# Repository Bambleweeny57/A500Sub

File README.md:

# **A500Sub — Amiga A500+ Rev 8A.2 (KiCad Reconstruction)**

A full KiCad reconstruction of the **Commodore Amiga A500+ Rev 8A.2** motherboard, supported with a complete BOM, 3D models, and reference images.  
This project preserves the A500+ Rev 8A.2 board layout in an editable, open format for restoration, repair, and hardware exploration.

---

## 🧭 Project Purpose

The goal of this repository is to provide a clean, accurate, and reproducible version of the **A500+ Rev 8A.2** motherboard for:

- Restoring original A500+ systems  
- Building new boards from scratch  
- Hardware repair and diagnostics  
- Long‑term preservation of Commodore’s design  
- Modding, expansion, and experimentation  

All Gerbers and KiCad sources are included for manufacturing and study.

---

## 📁 Repository Structure

| Folder / File | Description |
|---------------|-------------|
| **`/src`** | Full KiCad project for the A500+ Rev 8A.2 board |
| **`/gerbers`** | Ready‑to‑manufacture Gerber set |
| **`/bom`** | Bill of Materials for component sourcing |
| **`/images`** | Board renders, 3D views, and reference images |
| **`Submeson A500+ gerbers.zip`** | Packaged Gerber archive for PCB fabrication |

---

## 🛠️ Features

### **✔️ Complete KiCad Reconstruction**
- Editable PCB layout  
- Accurate trace routing  
- Includes footprints, netlist, and 3D models  
- Suitable for fabrication without modification  

### **✔️ Manufacturing‑Ready Gerbers**
- Clean, validated Gerber set  
- Provided both in the `/gerbers` folder and as a ZIP archive  

### **✔️ Full BOM Included**
- Component list for building the board  
- Helps with sourcing legacy and modern‑equivalent parts  

### **✔️ 3D Models & Renders**
- Visual reference for assembly  
- Useful for verifying component placement and clearances  

---

## 🧩 About the Amiga A500+ Rev 8A.2

The **A500+** was the final revision of the classic Amiga 500 line, featuring:

- ECS chipset  
- 1 MB Chip RAM  
- Battery‑backed RTC  
- Updated motherboard layout  
- Improved memory and expansion handling  

Rev 8A.2 is one of the later, more stable board revisions, making it ideal for restoration and reproduction.

---

## 🚀 How to Use This Project

### **Open in KiCad**
```bash
git clone https://github.com/Bambleweeny57/A500Sub
```
Open

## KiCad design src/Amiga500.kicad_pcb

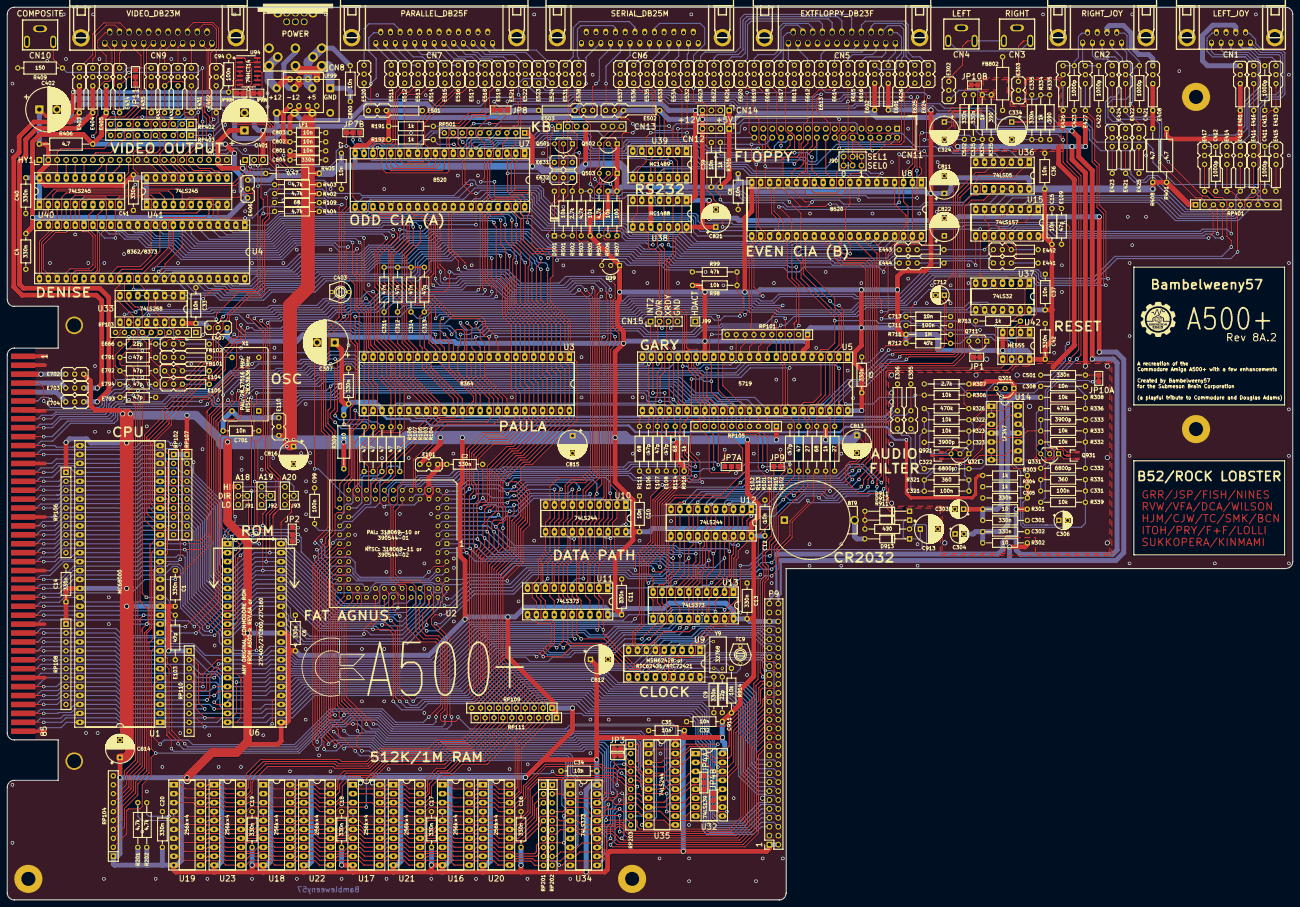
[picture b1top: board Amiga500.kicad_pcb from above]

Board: 2 copper layers, 365.8 x 254.0 mm, 365 parts (0 on the bottom side), 471 nets.

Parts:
BT9: CR2032; Battery_Holder_Coin_2032_BS-7
C1, C2, C3, C4, C5, C6, C9, C11, C13, C14, C16, C17, C18, C19, C20, C40, C41, C42, C804: 330n; C_Axial_L6.3mm_D2.5mm_P10.16mm
C7, C8, C10, C12, C15, C32, C33, C34, C35, C36, C37, C701, C800, C801, C802, C803: 10n; C_Axial_L6.3mm_D2.5mm_P10.16mm
C39, C308, C713: 10n; C_Axial_L9.0mm_D3.2mm_P12.70mm
C94, C99: 100n; C_Axial_L6.3mm_D2.5mm_P10.16mm
C301, C302, C305, C325, C335, C501, C502: 330n; C_Axial_L9.0mm_D3.2mm_P12.70mm
C303, C304: 22u; CP_Radial_D5.0mm_P2.50mm
C306, C712: 10u; CP_Radial_D5.0mm_P2.50mm
C307, C401, C402: 1000u; CP_Radial_D12.5mm_P5.00mm
C311, C312, C313, C314: 47n; C_Axial_L9.0mm_D3.2mm_P12.70mm
C321, C331, C711: 100n; C_Axial_L9.0mm_D3.2mm_P12.70mm
C322, C332: 6800p; C_Axial_L9.0mm_D3.2mm_P12.70mm
C323, C333: 3900p; C_Axial_L9.0mm_D3.2mm_P12.70mm
C324, C334: 22u; CP_Radial_D8.0mm_P5.00mm
C403: 47p; VariCap
C411, C412, C413, C421, C422, C423: 1000p; C_Axial_L9.0mm_D3.2mm_P12.70mm
C811, C812, C813, C814, C815, C816: 100u; CP_Radial_D8.0mm_P5.00mm
C821, C822: 47u; CP_Radial_D8.0mm_P5.00mm
C911: 22p; C_Axial_L6.3mm_D2.5mm_P10.16mm
C913: 4.7u; CP_Radial_D8.0mm_P5.00mm
CN1: LEFT_JOY; DB_9M
CN2: RIGHT_JOY; DB_9M
CN3: RIGHT; SWITCHCRAFT_PJRAN1X1U01X
CN4: LEFT; SWITCHCRAFT_PJRAN1X1U01X
CN5: EXTFLOPPY_DB23F; DB_23F
CN6: SERIAL_DB25M; DB_25M
CN7: PARALLEL_DB25F; DB_25F
CN8: POWER; DS215+DIN8_COMBO
CN9: VIDEO_DB23M; DB_23M
CN10: COMPOSITE; SWITCHCRAFT_PJRAN1X1U01X
CN11: INTERNAL_FLOPPY; IDC-Header_2x17_P2.54mm_Vertical
CN12: FLOPPY_POWER; PinHeader_1x04_P2.54mm_Vertical
CN13: KEYBOARD; Keyboard_Connector
CN14: IDE_POWER; PinHeader_1x04_P2.54mm_Vertical
CN15: IDE_I/F; PinHeader_1x04_P2.54mm_Vertical
D501: 1N4148; D_DO-35_SOD27_P12.70mm_Horizontal
D911, D912, D913: 1n4148; D_DO-35_SOD27_P12.70mm_Horizontal
E101, E110, E406, E407, E702, E703, E704: 10n; EMI_Filter_Short
E102, E103, E106, E107, E108: 47p; C_Axial_L9.0mm_D3.2mm_P12.70mm
E104, E105: 68; EMI_Filter_Long
E109, E791, E792, E793, E794: 47p; C_Axial_L6.3mm_D2.5mm_P10.16mm
E302, E303: 6800p; EMI_Filter_Short
E305, E306: 270p; EMI_Filter_Long
E401, E403, E404, E405, E408, E601, E602: 10n; EMI_Filter_Long
E402, E434: 150p; EMI_Filter_Long
E411, E412, E413, E414, E421, E422, E423, E424: 6800p; EMI_Filter_Long
E415, E416, E417, E425, E426, E427, E441, E442, E443, E444: 470p; EMI_Filter_Long
E431, E432, E433, E435: FERR; EMI_Filter_Long
E501, E502, E503: 47 1/2W; EMI_Filter_Longer
E511, E512, E513, E514, E515, E516, E517, E518, E519, E521, E522, E523, E524, E611, E612, E613, E614, E615, E616, E617, E618, E619, E620, E621, E622, E623, E624, E625, E626, E631, E632: 100p; EMI_Filter_Short
E520, E531, E533, E535, E536, E537, E538: 470p; EMI_Filter_Short
E532, E534: 150p; EMI_Filter_Short
E666: 22p; C_Axial_L6.3mm_D2.5mm_P10.16mm
FB101: 68; EMI_Filter_Long
FB102: 150; EMI_Filter_Long
FB802: Ferrite_Bead_Small; Ferrite_Axial_L9.0mm_D3.2mm_P12.70mm
HY1: VIDIOT; PinHeader_1x22_P2.54mm_Vertical
HY2: COLOR_ANNEX; PinHeader_1x03_P2.54mm_Vertical
J90: DRIVE_SWITCHER; DriveSwitchHeader
J91, J92, J93: Dispatcher_3to1
J99: CONN_HDACT; PinHeader_1x01_P2.54mm_Vertical
JP1, JP3A1, JP3B1, JP10A1, JP10B1, JP99H1, JP99V1: Jumper_2_Bridged; Jumper2-Bridged
JP2, JP7B1, JP8: Jumper_3_Bridged23; Jumper3-Bridged23
JP4A1, JP4B1, JP7A1: Jumper_3_Open; Jumper3-Open
JP9: Jumper_2_Open; Jumper2-Open
JP11: Jumper_3_Bridged12; Jumper3-Bridged12
LF1: L; LineFilter
LF99: CM4545Z131B-10
MT1, MT2, MT4, MT5, MT6, MT7: MountingHole_Pad; MountingHole_4mm_Pad
P1: EXPANSION BUS; A2000_COPRO_SLOT
P9: TRAPDOOR; Trapdoor
Q99, Q301, Q502, Q503: 2N3906; TO-92L_Inline_Wide
Q321, Q331: MPF102; TO-92L_Inline_Wide
Q501, Q711: 2N3904; TO-92L_Inline_Wide
Q921, Q931: MMBFJ113; SOT-23_LongerPads
R98, R306, R308, R322, R323, R332, R333, R339, R501, R505, R506, R914: 10k; R_Axial_DIN0309_L9.0mm_D3.2mm_P12.70mm_Horizontal
R99, R712: 47k; R_Axial_DIN0309_L9.0mm_D3.2mm_P12.70mm_Horizontal
R101, R102: 27; R_Axial_DIN0309_L9.0mm_D3.2mm_P12.70mm_Horizontal
R103, R104, R105, R106, R107, R113: 47; R_Axial_DIN0309_L9.0mm_D3.2mm_P12.70mm_Horizontal
R109, R111, R112, R114: 68; R_Axial_DIN0309_L9.0mm_D3.2mm_P12.70mm_Horizontal
R191, R192, R303, R304, R305, R324, R334, R713, R915, R916: 1k; R_Axial_DIN0309_L9.0mm_D3.2mm_P12.70mm_Horizontal
R201, R202, R402, R403, R404, R503, R504: 4.7k; R_Axial_DIN0309_L9.0mm_D3.2mm_P12.70mm_Horizontal
R301, R302: 10; R_Axial_DIN0309_L9.0mm_D3.2mm_P12.70mm_Horizontal
R307, R502: 2.7k; R_Axial_DIN0309_L9.0mm_D3.2mm_P12.70mm_Horizontal
R309: 10; R_Axial_DIN0309_L9.0mm_D3.2mm_P15.24mm_Horizontal
R321, R331: 360; R_Axial_DIN0309_L9.0mm_D3.2mm_P12.70mm_Horizontal
R325, R335: 390; R_Axial_DIN0309_L9.0mm_D3.2mm_P12.70mm_Horizontal
R326, R336: 470k; R_Axial_DIN0309_L9.0mm_D3.2mm_P12.70mm_Horizontal
R401, R406, R408: 4.7; R_Axial_DIN0309_L9.0mm_D3.2mm_P15.24mm_Horizontal
R405: 0.47; R_Axial_DIN0309_L9.0mm_D3.2mm_P15.24mm_Horizontal
R409: 150; R_Axial_DIN0309_L9.0mm_D3.2mm_P12.70mm_Horizontal
R507: 100; R_Axial_DIN0309_L9.0mm_D3.2mm_P12.70mm_Horizontal
R711: 1M; R_Axial_DIN0309_L9.0mm_D3.2mm_P12.70mm_Horizontal
R911: 470; R_Axial_DIN0309_L9.0mm_D3.2mm_P12.70mm_Horizontal
RP101, RP102, RP105, RP106, RP107, RP108, RP109, RP110, RP111: 4.7k; R_Array_SIP10
RP103: 39; R_Array_SIP10
RP104: 470; R_Array_SIP10
RP201, RP202, RP203: 68; R_Array_SIP10
RP401: 4.7K; R_Array_SIP10
RP402, RP403: 47; R_Array_SIP10
RP501: 10k; R_Array_SIP10
TC9: 6.8-45p; VariCap
U1: 68000D; DIP-64_W22.86mm_Socket_LongPads
U2: FAT_AGNUS_8375; PLCC-84_THT-Socket
U3: PAULA; DIP-48_W15.24mm_Socket_LongPads
U4: DENISE; DIP-48_W15.24mm_Socket_LongPads
U5: GARY_5719; DIP-48_W15.24mm_Socket_LongPads
U6: ROM; DIP-42_W15.24mm_Socket_LongPads
U7, U8: VIA_8520; DIP-40_W15.24mm_Socket_LongPads
U9: MSM6242B; DIP-18_W7.62mm_Socket_LongPads
U10, U12, U35: 74LS244; DIP-20_W7.62mm_Socket_LongPads
U11, U13, U34: 74LS373; DIP-20_W7.62mm_Socket_LongPads
U14: LF347; DIP-14_W7.62mm_Socket_LongPads
U15: 74LS157; DIP-16_W7.62mm_Socket_LongPads
U16, U17, U18, U19, U20, U21, U22, U23: XX4256; DIP-20_W7.62mm_Socket_LongPads
U32: 74LS139; DIP-16_W7.62mm_Socket_LongPads
U33: 74LS258; DIP-16_W7.62mm_Socket_LongPads
U36: 74LS05; DIP-14_W7.62mm_Socket_LongPads
U37: 74LS32; DIP-14_W7.62mm_Socket_LongPads
U38: MC1488; DIP-14_W7.62mm_Socket_LongPads
U39: MC1489; DIP-14_W7.62mm_Socket_LongPads
U40, U41: 74LS245; DIP-20_W7.62mm_Socket_LongPads
U42: NE555; DIP-8_W7.62mm_Socket_LongPads
U94: 74HCT14; SOIC-14_3.9x8.7mm_P1.27mm
X1: XTAL; Oscillator_DIP-14
Y9: 32768; Crystal_RTC

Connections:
7MHZ: E103.1, P1.7, R106.1, U1.15
7MHZ_A: C403.1, E794.1, R107.1, U4.35
+12V: C802.1, C821.1, CN12.4, CN14.4, E404.1, E502.1, E602.1, E704.1, HY2.3, LF1.5, LF99.5, P9.55, R301.1, R911.2, U38.14
+VDC: C301.1, C303.1, Q301.1, R301.2, R307.2, U14.4
-12V: C803.2, C822.2, E403.1, E503.1, E703.1, LF1.6, LF99.6, P9.56, R302.2, U38.1
-VDC: C302.2, C304.2, R302.1, R308.2, U14.11
/Denise & Video Stuff/ab: E433.1, HY1.17
/Denise & Video Stuff/ag: E432.1, HY1.12
/Denise & Video Stuff/ar: E431.1, HY1.7
/Denise & Video Stuff/bb0: HY1.16, RP402.3, U41.15
/Denise & Video Stuff/bb1: HY1.15, U41.16
/Denise & Video Stuff/bb2: HY1.14, U41.17
/Denise & Video Stuff/bb3: HY1.13, RP402.5, U41.18
/Denise & Video Stuff/bcck: HY2.1, RP403.4, U41.14
/Denise & Video Stuff/bcsync_a: RP403.9, U41.12
/Denise & Video Stuff/bcsync_b: HY1.18, U41.11
/Denise & Video Stuff/bg0: HY1.11, U40.11
/Denise & Video Stuff/bg1: HY1.10, U40.12
/Denise & Video Stuff/bg2: HY1.9, U40.13
/Denise & Video Stuff/bg3: HY1.8, RP402.7, U40.14
/Denise & Video Stuff/bpixelsw: RP402.1, U41.13
/Denise & Video Stuff/br0: HY1.6, U40.15
/Denise & Video Stuff/br1: HY1.5, U40.16
/Denise & Video Stuff/br2: HY1.4, U40.17
/Denise & Video Stuff/br3: HY1.3, RP402.9, U40.18
/Denise & Video Stuff/cck_c: E402.1, RP403.3
/Denise & Video Stuff/csync_out: E434.1, JP11.2
/Denise & Video Stuff/hsync_buf: JP99H1.2, RP403.5, U94.6
/Denise & Video Stuff/rbcsync_a: JP11.1, RP403.10
/Denise & Video Stuff/vsync_buf: JP99V1.2, RP403.7, U94.8
/Kickstart ROM/a18_rom: J91.4, U6.2
/Kickstart ROM/a19_rom: J92.4, U6.1
/Kickstart ROM/a20_rom: J93.4, U6.42
/Parallel & Serial/+v: CN6.9, E502.3
/Parallel & Serial/-v: CN6.10, E503.3
/Parallel & Serial/cd: CN6.8, E537.3
/Parallel & Serial/clock: CN13.1, E632.1
/Parallel & Serial/cts: CN6.5, E535.3
/Parallel & Serial/data: CN13.2, E631.1
/Parallel & Serial/dsr: CN6.6, E536.3
/Parallel & Serial/dtr: CN6.20, E531.3
/Parallel & Serial/inuse: CN13.8, Q99.3, Q503.3
/Parallel & Serial/pp0: E512.1, U7.10
/Parallel & Serial/pp1: E513.1, U7.11
/Parallel & Serial/pp2: E514.1, U7.12
/Parallel & Serial/pp3: E515.1, U7.13
/Parallel & Serial/pp4: E516.1, U7.14
/Parallel & Serial/pp5: E517.1, U7.15
/Parallel & Serial/pp6: E518.1, U7.16
/Parallel & Serial/pp7: E519.1, U7.17
/Parallel & Serial/rts: CN6.4, E533.3
/Parallel & Serial/rxd: CN6.3, E534.3
/Parallel & Serial/sel0_out: J90.1, J90.2, U8.13
/Parallel & Serial/sel1_out: J90.5, J90.6, U8.14
/Parallel & Serial/status: CN13.7, Q502.3, R507.1
/Parallel & Serial/txd: CN6.2, E532.3
/Parallel & Serial/~auto: CN7.14, E501.3
/Parallel & Serial/~init: CN7.16, E520.3
/Paula & Audio Stuff/down1: CN1.2, E412.3
/Paula & Audio Stuff/down2: CN2.2, E422.3
/Paula & Audio Stuff/fire1: C411.1, CN1.6, E415.3
/Paula & Audio Stuff/fire2: C421.1, CN2.6, E425.3
/Paula & Audio Stuff/left: E306.1, U3.31
/Paula & Audio Stuff/left1: CN1.3, E413.3
/Paula & Audio Stuff/left2: CN2.3, E423.3
/Paula & Audio Stuff/pot0x: C311.1, E417.1, U3.32
/Paula & Audio Stuff/pot0y: C312.1, E416.1, U3.33
/Paula & Audio Stuff/pot1x: C313.1, E427.1, U3.35
/Paula & Audio Stuff/pot1y: C314.1, E426.1, U3.36
/Paula & Audio Stuff/potx1: C412.1, CN1.5, E417.3
/Paula & Audio Stuff/potx2: C422.1, CN2.5, E427.3
/Paula & Audio Stuff/poty1: C413.1, CN1.9, E416.3
/Paula & Audio Stuff/poty2: C423.1, CN2.9, E426.3
/Paula & Audio Stuff/right: E305.1, U3.30
/Paula & Audio Stuff/right1: CN1.4, E414.3
/Paula & Audio Stuff/right2: CN2.4, E424.3
/Paula & Audio Stuff/up1: CN1.1, E411.3
/Paula & Audio Stuff/up2: CN2.1, E421.3
/Paula & Audio Stuff/vcc1: CN1.7, E401.3
/Paula & Audio Stuff/vcc2: CN2.7, E408.3
/RAM/ma0: RP202.3, U16.6, U17.6, U18.6, U19.6, U20.6, U21.6, U22.6, U23.6
/RAM/ma1: RP202.5, U16.7, U17.7, U18.7, U19.7, U20.7, U21.7, U22.7, U23.7
/RAM/ma2: RP202.7, U16.8, U17.8, U18.8, U19.8, U20.8, U21.8, U22.8, U23.8
/RAM/ma3: RP202.10, U16.9, U17.9, U18.9, U19.9, U20.9, U21.9, U22.9, U23.9
/RAM/ma4: RP201.10, U16.11, U17.11, U18.11, U19.11, U20.11, U21.11, U22.11, U23.11
/RAM/ma5: RP201.8, U16.12, U17.12, U18.12, U19.12, U20.12, U21.12, U22.12, U23.12
/RAM/ma6: RP201.5, U16.13, U17.13, U18.13, U19.13, U20.13, U21.13, U22.13, U23.13
/RAM/ma7: RP201.3, U16.14, U17.14, U18.14, U19.14, U20.14, U21.14, U22.14, U23.14
/RAM/ma8: RP202.1, U16.15, U17.15, U18.15, U19.15, U20.15, U21.15, U22.15, U23.15
/RAM/~bcasl0: JP4A1.1, RP203.7, U32.4
/RAM/~bcasu0: JP4B1.1, RP203.5, U32.12
A1: P1.29, RP107.9, U1.29, U2.60, U6.10
A2: P1.27, P9.45, RP107.8, U1.30, U2.61, U6.9, U9.4
A3: P1.26, P9.46, RP107.7, U1.31, U2.62, U6.8, U9.5
A4: P1.24, P9.47, RP107.6, U1.32, U2.63, U6.7, U9.6
A5: P1.21, P9.48, RP107.5, U1.33, U2.64, U6.6, U9.7
A6: P1.23, RP107.4, U1.34, U2.65, U6.5
A7: P1.28, RP107.2, U1.35, U2.66, U6.4
A8: P1.30, RP107.3, U1.36, U2.67, U6.3, U7.38, U8.38
A9: P1.32, RP106.2, U1.37, U2.68, U6.41, U7.37, U8.37
A10: P1.34, RP106.3, U1.38, U2.69, U6.40, U7.36, U8.36
A11: P1.36, RP106.4, U1.39, U2.70, U6.39, U7.35, U8.35
A12: P1.38, RP106.5, U1.40, U2.71, U6.38, U37.1
A13: P1.39, RP106.6, U1.41, U2.72, U6.37, U37.4
A14: P1.41, RP106.7, U1.42, U2.73, U6.36
A15: P1.43, RP106.8, U1.43, U2.74, U6.35, U36.13
A16: P1.45, RP106.9, U1.44, U2.75, U6.34
A17: P1.47, RP105.8, U1.45, U2.76, U5.33, U6.33
A18: J91.2, P1.52, RP105.7, U1.46, U2.77, U5.34
A19: J92.2, JP2.3, P1.54, RP105.6, U1.47, U5.35
A20: J93.2, P1.56, RP105.5, U1.48, U2.35, U5.36
A21: P1.58, RP105.4, U1.50, U5.37
A22: P1.57, RP105.3, U1.51, U5.38
A23: JP2.1, P1.59, RP105.2, U1.52, U5.39
AUDIN: C501.1, JP10A1.1
AUDOUT: C502.2, JP10B1.2
BDRA0: P9.23, RP202.4, U35.9
BDRA1: P9.24, RP202.6, U35.7
BDRA2: P9.25, RP202.8, U34.9
BDRA3: P9.26, RP202.9, U34.19
BDRA4: P9.27, RP201.9, U34.16
BDRA5: P9.28, RP201.7, U34.6
BDRA6: P9.29, RP201.6, U34.15
BDRA7: P9.30, RP201.4, U34.5
BDRA8: P9.31, RP202.2, U34.12
BDRA9: U32.2, U32.14, U34.2
CCK: E108.1, R103.1, U3.28, U4.36, U5.28, U33.5, U33.6, U35.15, U41.6
CCKQ: E107.1, R104.1, U3.29, U5.27, U33.10, U33.11
CDAC: E793.1, P1.15, RP103.4
D0: P1.75, P9.41, RP110.5, U1.5, U6.14, U7.33, U9.14, U10.2, U11.2
D1: P1.77, P9.42, RP110.6, U1.4, U6.16, U7.32, U9.13, U10.4, U11.5
D2: P1.79, P9.43, RP110.7, U1.3, U6.18, U7.31, U9.12, U10.6, U11.6
D3: P1.81, P9.44, RP110.8, U1.2, U6.20, U7.30, U9.11, U10.8, U11.9
D4: P1.83, RP110.9, U1.1, U6.23, U7.29, U10.11, U11.12
D5: P1.86, RP110.4, U1.64, U6.25, U7.28, U10.13, U11.15
D6: P1.84, RP110.3, U1.63, U6.27, U7.27, U10.15, U11.16
D7: P1.82, RP110.2, U1.62, U6.29, U7.26, U10.17, U11.19
D8: P1.80, RP108.9, U1.61, U6.15, U8.33, U12.2, U13.2
D9: P1.78, RP108.8, U1.60, U6.17, U8.32, U12.4, U13.5
D10: P1.76, RP108.7, U1.59, U6.19, U8.31, U12.6, U13.6
D11: P1.71, RP108.6, U1.58, U6.21, U8.30, U12.8, U13.9
D12: P1.69, RP108.5, U1.57, U6.24, U8.29, U12.11, U13.12
D13: P1.67, RP108.4, U1.56, U6.26, U8.28, U12.13, U13.15
D14: P1.65, RP108.3, U1.55, U6.28, U8.27, U12.15, U13.16
D15: P1.63, RP108.2, U1.54, U6.30, U8.26, U12.17, U13.19
DIR: CN11.18, E623.1, U8.11
DKWE: U3.39, U5.8
DMAL: U2.18, U3.12
DRA0: U2.42, U35.11
DRA1: U2.43, U35.13
DRA2: U2.44, U34.8
DRA3: U2.45, U34.18
DRA4: U2.46, U34.17
DRA5: U2.47, U34.7
DRA6: U2.48, U34.14
DRA7: U2.49, U34.4
DRA8: U2.50, U34.13
DRA9: U2.55, U34.3
DRD0: P9.5, RP111.2, U2.14, U3.10, U4.7, U10.18, U11.3, U16.18, U20.18
DRD1: P9.6, RP109.2, U2.13, U3.9, U4.6, U10.16, U11.4, U16.2, U20.2
DRD2: P9.7, RP111.3, U2.12, U3.7, U4.5, U10.14, U11.7, U16.19, U20.19
DRD3: P9.8, RP109.3, U2.11, U3.6, U4.4, U10.12, U11.8, U16.1, U20.1
DRD4: P9.9, RP111.4, U2.10, U3.5, U4.3, U10.9, U11.13, U17.18, U21.18
DRD5: P9.10, RP109.4, U2.9, U3.4, U4.2, U10.7, U11.14, U17.2, U21.2
DRD6: P9.11, RP111.5, U2.8, U3.3, U4.1, U10.5, U11.17, U17.19, U21.19
DRD7: P9.12, RP109.5, U2.7, U3.2, U4.48, U10.3, U11.18, U17.1, U21.1
DRD8: P9.13, RP111.6, U2.6, U3.1, U4.47, U12.18, U13.3, U18.18, U22.18
DRD9: P9.14, RP109.6, U2.5, U3.48, U4.46, U12.16, U13.4, U18.2, U22.2
DRD10: P9.15, RP111.7, U2.4, U3.47, U4.45, U12.14, U13.7, U18.19, U22.19
DRD11: P9.16, RP109.7, U2.3, U3.46, U4.44, U12.12, U13.8, U18.1, U22.1
DRD12: P9.17, RP111.8, U2.2, U3.45, U4.43, U12.9, U13.13, U19.18, U23.18
DRD13: P9.18, RP109.8, U2.1, U3.44, U4.42, U12.7, U13.14, U19.2, U23.2
DRD14: P9.19, RP111.9, U2.84, U3.43, U4.41, U12.5, U13.17, U19.19, U23.19
DRD15: P9.20, RP109.9, U2.83, U3.42, U4.40, U12.3, U13.18, U19.1, U23.1
E: P1.50, R109.2, U1.20
FC0: P1.31, RP102.4, U1.28
FC1: P1.33, RP102.5, U1.27
FC2: P1.35, RP102.6, U1.26
GND: BT9.2, C1.2, C2.2, C3.2, C4.2, C5.2, C6.2, C7.2, C8.2, C9.2, C10.2, C11.2, C12.2, C13.2, C14.2, C15.2, C16.2, C17.2, C18.2, C19.2, C20.2, C32.2, C33.2, C34.2, C35.2, C36.2, C37.2, C39.2, C40.2, C41.2, C42.2, C94.2, C99.2, C307.2, C401.2, C402.2, C403.2, C411.2, C412.2, C413.2, C421.2, C422.2, C423.2, C701.2, C711.2, C712.2, C713.2, C801.e, C802.2, C803.1, C804.2, C811.2, C812.2, C813.2, C814.2, C815.2, C816.2, C821.2, C822.1, C911.1, C913.2, CN1.0, CN1.8, CN2.0, CN2.8, CN3.1, CN4.1, CN5.0, CN5.3, CN5.4, CN5.5, CN5.6, CN5.7, CN6.0, CN6.7, CN7.0, CN7.17, CN7.18, CN7.19, CN7.20, CN7.21, CN7.22, CN7.23, CN7.24, CN7.25, CN8.2, CN8.6, CN9.0, CN9.13, CN9.16, CN9.17, CN9.18, CN9.19, CN9.20, CN10.1, CN11.1, CN11.5, CN11.7, CN11.9, CN11.11, CN11.13, CN11.15, CN11.17, CN11.19, CN11.21, CN11.23, CN11.25, CN11.27, CN11.29, CN11.31, CN11.33, CN12.2, CN12.3, CN13.6, CN14.2, CN14.3, CN15.4, D501.2, E101.2, E102.2, E103.2, E104.2, E105.2, E106.2, E107.2, E108.2, E109.2, E110.2, E302.2, E303.2, E401.2, E402.2, E403.2, E404.2, E405.2, E406.2, E407.2, E408.2, E411.2, E412.2, E413.2, E414.2, E415.2, E416.2, E417.2, E421.2, E422.2, E423.2, E424.2, E425.2, E426.2, E427.2, E431.2, E432.2, E433.2, E434.2, E435.2, E441.2, E442.2, E443.2, E444.2, E501.2, E502.2, E503.2, E511.2, E512.2, E513.2, E514.2, E515.2, E516.2, E517.2, E518.2, E519.2, E520.2, E521.2, E522.2, E523.2, E524.2, E531.2, E532.2, E533.2, E534.2, E535.2, E536.2, E537.2, E538.2, E601.2, E602.2, E611.2, E612.2, E613.2, E614.2, E615.2, E616.2, E617.2, E618.2, E619.2, E620.2, E621.2, E622.2, E623.2, E624.2, E625.2, E626.2, E631.2, E632.2, E666.2, E702.2, E703.2, E704.2, E791.2, E792.2, E793.2, E794.2, FB101.2, FB102.2, FB802.2, HY1.1, HY1.22, J91.3, J92.3, J93.3, JP7A1.1, JP9.1, LF1.8, LF99.8, MT1.1, MT2.1, MT4.1, MT5.1, MT6.1, MT7.1, P1.1, P1.2, P1.3, P1.4, P1.12, P1.13, P1.25, P1.37, P1.49, P1.61, P1.73, P1.85, P9.3, P9.4, P9.21, P9.22, P9.34, P9.53, P9.54, Q501.1, Q711.1, R409.2, R501.1, RP101.10, RP102.10, RP104.10, RP105.10, RP106.10, RP107.10, RP108.10, RP109.10, RP110.10, RP111.10, RP401.10, TC9.2, U1.16, U1.53, U2.41, U2.58, U2.82, U3.8, U4.37, U5.1, U5.24, U5.40, U6.11, U6.12, U6.31, U7.1, U8.1, U9.9, U10.10, U11.10, U12.10, U13.10, U15.8, U15.15, U16.16, U16.20, U17.16, U17.20, U18.16, U18.20, U19.16, U19.20, U20.16, U20.20, U21.16, U21.20, U22.16, U22.20, U23.16, U23.20, U32.8, U33.8, U33.15, U34.1, U34.10, U35.1, U35.10, U35.19, U36.7, U37.7, U37.10, U37.13, U38.7, U39.7, U40.10, U40.19, U41.10, U41.19, U42.1, U94.7, X1.1, X1.7
GNDA: C301.2, C302.1, C303.2, C304.1, C305.2, C306.2, C308.2, C311.2, C312.2, C313.2, C314.2, C323.2, C333.2, E305.2, E306.2, FB802.1, R304.1, R325.2, R335.2, U3.34
M0H: E443.3, U4.9
M0V: E441.3, U4.38
M1H: E442.3, U4.8
M1V: E444.3, U4.39
unnamed: BT9.1, D913.2
unnamed: C2.1, E101.3, U2.15
unnamed: C3.1, C307.1, R303.2, R309.2, U3.27
unnamed: C9.1, C913.1, D912.1, D913.1, U9.18
unnamed: C33.1, E407.3, U33.16
unnamed: C99.1, U2.40
unnamed: C308.1, Q301.3, R308.1, R326.2, R336.2
unnamed: C321.1, Q321.1, Q921.1, R321.1, R322.2, U14.14
unnamed: C321.2, E306.3, R321.2, U14.13
unnamed: C322.1, C324.1, C325.2, U14.1, U14.2
unnamed: C322.2, R322.1, R323.2
unnamed: C323.1, Q321.2, Q921.2, R323.1, U14.3
unnamed: C324.2, C325.1, JP10B1.1, R324.2
unnamed: C331.1, Q331.1, Q931.1, R331.1, R332.2, U14.8
unnamed: C331.2, E305.3, R331.2, R339.1, U14.9
unnamed: C332.1, C334.1, C335.2, U14.6, U14.7
unnamed: C332.2, R332.1, R333.2
unnamed: C333.1, Q331.2, Q931.2, R333.1, U14.5
unnamed: C334.2, C335.1, R334.2
unnamed: C401.1, HY1.21, R405.2
unnamed: C501.2, CN6.18
unnamed: C502.1, CN6.11
unnamed: C701.1, E110.3, X1.14
unnamed: C711.1, R711.1, U42.2
unnamed: C712.1, R712.1, U42.6, U42.7
unnamed: C713.1, U42.5
unnamed: C800.1, CN8.4, LF1.1, LF99.1
unnamed: C800.2, CN8.1, LF1.2, LF99.2
unnamed: C911.2, U9.17, Y9.3
unnamed: CN3.2, CN4.3, E303.3
unnamed: CN3.3, CN4.2, E302.3
unnamed: CN5.1, E611.3
unnamed: CN5.2, E612.3
unnamed: CN5.8, E613.3
unnamed: CN5.9, E614.3
unnamed: CN5.10, E615.3
unnamed: CN5.11, E616.3
unnamed: CN5.12, E601.3
unnamed: CN5.13, E617.3
unnamed: CN5.14, E618.3
unnamed: CN5.15, E619.3
unnamed: CN5.16, E620.3
unnamed: CN5.17, E621.3
unnamed: CN5.18, E622.3
unnamed: CN5.19, E623.3
unnamed: CN5.20, E624.3
unnamed: CN5.21, E625.3
unnamed: CN5.22, E626.3
unnamed: CN5.23, E602.3
unnamed: CN6.22, E538.3
unnamed: CN7.1, E511.3
unnamed: CN7.2, E512.3
unnamed: CN7.3, E513.3
unnamed: CN7.4, E514.3
unnamed: CN7.5, E515.3
unnamed: CN7.6, E516.3
unnamed: CN7.7, E517.3
unnamed: CN7.8, E518.3
unnamed: CN7.9, E519.3
unnamed: CN7.10, E521.3
unnamed: CN7.11, E522.3
unnamed: CN7.12, E523.3
unnamed: CN7.13, E524.3
unnamed: CN8.3, LF1.4, LF99.4
unnamed: CN8.5, LF1.3, LF99.3
unnamed: CN9.1, RP403.2
unnamed: CN9.3, E431.3
unnamed: CN9.4, E432.3
unnamed: CN9.5, E433.3
unnamed: CN9.6, RP402.4
unnamed: CN9.7, RP402.6
unnamed: CN9.8, RP402.8
unnamed: CN9.9, RP402.10
unnamed: CN9.10, E434.3
unnamed: CN9.11, RP403.6
unnamed: CN9.12, RP403.8
unnamed: CN9.14, RP402.2
unnamed: CN9.15, E402.3
unnamed: CN9.21, E403.3
unnamed: CN9.22, E404.3
unnamed: CN9.23, E405.3
unnamed: CN10.2, E435.3, R409.1
unnamed: D501.1, Q501.2, R501.2, R502.2
unnamed: D911.2, D912.2, R911.1
unnamed: E104.1, RP103.5, U33.7
unnamed: E105.1, RP103.7, U33.9
unnamed: E302.1, R324.1, R325.1
unnamed: E303.1, R334.1, R335.1
unnamed: E401.1, R401.2
unnamed: E408.1, R408.2
unnamed: E411.1, RP401.8, U15.3
unnamed: E412.1, RP401.9, U15.6
unnamed: E413.1, RP401.7, U15.2
unnamed: E414.1, RP401.6, U15.5
unnamed: E421.1, RP401.5, U15.10
unnamed: E422.1, RP401.4, U15.13
unnamed: E423.1, RP401.3, U15.11
unnamed: E424.1, RP401.2, U15.14
unnamed: E435.1, HY1.19
unnamed: E441.1, U15.4
unnamed: E442.1, U15.12
unnamed: E443.1, U15.7
unnamed: E444.1, U15.9
unnamed: E511.1, RP501.10, U7.18
unnamed: E521.1, RP501.6, U7.24
unnamed: E522.1, U8.2, U8.39
unnamed: E523.1, U8.3, U8.40
unnamed: E524.1, Q501.3, RP501.4, U8.4
unnamed: E531.1, U38.11
unnamed: E532.1, U38.8
unnamed: E533.1, U38.6
unnamed: E534.1, U39.1
unnamed: E535.1, U39.4
unnamed: E536.1, U39.10
unnamed: E537.1, U39.13
unnamed: E538.1, R502.1
unnamed: E666.1, FB102.3, U2.34
unnamed: E702.3, P1.5, P1.6
unnamed: E703.3, P1.8
unnamed: E704.3, P1.10
unnamed: FB101.1, X1.8
unnamed: FB101.3, U33.13
unnamed: FB102.1, U33.12
unnamed: HY1.20, JP11.3
unnamed: HY2.2, U4.18
unnamed: J99.1, R98.2, R99.2
unnamed: JP1.1, Q711.3
unnamed: JP2.2, U2.59
unnamed: JP3A1.2, U35.16
unnamed: JP3B1.1, U35.18
unnamed: JP4A1.2, U35.14
unnamed: JP4B1.2, U35.12
unnamed: JP7A1.3, P9.32
unnamed: JP7B1.2, U7.19
unnamed: JP10A1.2, R339.2
unnamed: Q99.2, R99.1
unnamed: Q301.2, R306.1, R307.1
unnamed: Q321.3, Q921.3, R326.1
unnamed: Q331.3, Q931.3, R336.1
unnamed: Q502.2, R503.1
unnamed: Q503.2, R504.1
unnamed: Q711.2, R713.1
unnamed: R101.1, U5.43
unnamed: R102.1, U5.2
unnamed: R103.2, U2.39
unnamed: R104.2, U2.38
unnamed: R105.2, U2.36
unnamed: R106.2, R107.2, U2.37
unnamed: R109.1, U7.25, U8.25
unnamed: R111.1, U5.25
unnamed: R111.2, U11.11, U13.11
unnamed: R112.1, U5.3
unnamed: R112.2, U11.1, U13.1
unnamed: R113.1, U5.4
unnamed: R113.2, U10.1, U10.19, U12.1, U12.19
unnamed: R114.2, U5.21
unnamed: R201.2, RP203.2, U16.4, U16.5, U17.4, U17.5, U18.4, U18.5, U19.4, U19.5, U20.5, U21.5, U22.5, U23.5
unnamed: R202.2, RP203.4, U20.4, U21.4, U22.4, U23.4
unnamed: R306.2, U38.3
unnamed: R713.2, U42.3
unnamed: R914.2, U9.3, U9.15
unnamed: R915.2, U9.2, U36.10
unnamed: RP103.3, U33.4
unnamed: RP203.6, U18.17, U19.17, U22.17, U23.17
unnamed: RP203.8, U16.17, U17.17, U20.17, U21.17
unnamed: RP203.10, U16.3, U17.3, U18.3, U19.3, U20.3, U21.3, U22.3, U23.3
unnamed: TC9.1, U9.16, Y9.1
unnamed: U2.19, U5.19
unnamed: U2.20, U5.15
unnamed: U2.23, U5.18
unnamed: U2.25, U5.20
unnamed: U4.20, U40.5
unnamed: U4.21, U40.4
unnamed: U4.22, U40.3
unnamed: U4.23, U40.2
unnamed: U4.24, U41.5
unnamed: U4.25, U41.4
unnamed: U4.26, U41.3
unnamed: U4.27, U41.2
unnamed: U4.28, U40.9
unnamed: U4.29, U40.8
unnamed: U4.30, U40.7
unnamed: U4.31, U40.6
unnamed: U4.33, U41.7
unnamed: U9.1, Y9.2
unnamed: U32.1, U32.15, U34.11, U35.5
unnamed: U5.47, U36.1
unnamed: U5.46, U36.3
unnamed: U5.45, U36.5
unnamed: U5.44, U36.9
unnamed: U8.8, U38.4
unnamed: U8.9, U38.12
unnamed: U8.6, U39.6
unnamed: U8.5, U39.8
unnamed: U8.7, U39.11
unnamed: U94.4, U94.5
unnamed: U94.9, U94.10
OVL: RP101.9, U5.30, U7.2
RGA1: U2.33, U3.26, U4.17
RGA2: U2.32, U3.25, U4.16
RGA3: U2.31, U3.24, U4.15
RGA4: U2.30, U3.23, U4.14
RGA5: U2.29, U3.22, U4.13
RGA6: U2.28, U3.21, U4.12
RGA7: U2.27, U3.20, U4.11
RGA8: U2.26, U3.19, U4.10
R~W: P1.68, RP101.7, U1.9, U2.22, U5.12, U7.22, U8.22
VAC: C305.1, C306.1, R303.1, R304.2, U14.10, U14.12
VCC: C1.1, C5.1, C6.1, C7.1, C8.1, C10.1, C11.1, C12.1, C13.1, C14.1, C15.1, C16.1, C17.1, C18.1, C19.1, C20.1, C32.1, C34.1, C35.1, C36.1, C37.1, C39.1, C42.1, C801.1, C804.1, C811.1, C812.1, C813.1, C814.1, C815.1, C816.1, CN12.1, CN13.4, CN14.1, D911.1, E101.1, E110.1, E406.1, E407.1, E501.1, E601.1, E702.1, J91.1, J92.1, J93.1, LF1.7, LF99.7, P9.1, P9.2, P9.51, P9.52, Q99.1, Q502.1, Q503.1, R98.1, R191.1, R192.1, R201.1, R202.1, R305.1, R309.1, R401.1, R402.1, R403.1, R404.1, R405.1, R408.1, R505.2, R506.2, R507.2, R711.2, R712.2, R914.1, R915.1, R916.1, RP101.1, RP102.1, RP104.1, RP105.1, RP106.1, RP107.1, RP108.1, RP109.1, RP110.1, RP111.1, RP401.1, RP501.1, U1.14, U1.49, U5.6, U5.17, U5.48, U6.22, U6.32, U7.20, U8.20, U10.20, U11.20, U12.20, U13.20, U15.16, U16.10, U17.10, U18.10, U19.10, U20.10, U21.10, U22.10, U23.10, U32.16, U34.20, U35.20, U36.14, U37.14, U38.5, U38.10, U38.13, U39.14, U42.4, U42.8
VD: C40.1, C41.1, C94.1, C402.1, HY1.2, R406.1, U40.1, U40.20, U41.1, U41.20, U94.1, U94.13, U94.14
VDDA: C4.1, E405.1, E406.3, R406.2, U4.19
XCLK: R404.2, RP403.1, U33.14
XRDY: CN15.3, P1.18, RP104.8, U5.31
~AS: P1.74, RP101.8, U1.6, U2.24, U5.13
~BCASL1: JP4A1.3, P9.35, U32.5
~BCASU1: JP4B1.3, P9.36, U32.11
~BEER: P1.46, RP104.5, U1.22
~BGACK: P1.62, RP104.6, U1.12, U5.14
~BG: P1.64, U1.11
~BRAS0: JP3B1.2, P9.38, RP203.1
~BRAS1: JP3A1.1, P9.37, RP203.3
~BR: P1.60, RP104.7, U1.13
~BWE: P9.39, RP203.9, U35.3
~CASL: U2.53, U32.3, U35.6
~CASU: U2.54, U32.13, U35.8
~CCKQ_A: E105.3, E109.1, U15.1
~CCKQ: E791.1, P1.14, RP103.8
~CCK_A: E102.1, E104.3, P9.40
~CCK: E792.1, P1.16, RP103.6
~CDAC: E106.1, R105.1, U4.34, U5.26, U33.2, U33.3
~CHNG: CN11.2, E616.1, U7.4
~CLKCS: JP9.2, P9.33, R916.2, U36.11, U36.12
~CLKRD: P9.49, U5.22, U9.8
~CLKWR: P9.50, U5.23, U9.10
~CSYNC: U2.80, U4.32, U41.8, U41.9
~DKRD: CN11.30, E612.1, R305.2, U3.37
~DKWDB: CN11.22, E621.1, U36.6
~DKWD: U3.38, U5.9
~DKWEB: CN11.24, E620.1, U36.8
~DTACK: P1.66, R101.2, RP104.2, U1.10
~EVEN_CIA: U8.23, U37.6
~EXTICK: JP7A1.2, JP7B1.1, RP501.9, U5.32
~FIRE0: E415.1, JP8.1, U7.8
~FIRE1: E425.1, JP8.3, U7.9
~HLT: P1.55, RP101.3, U1.17, U5.42
~HSYNC: JP99H1.1, R402.2, U2.81, U8.19, U94.3
~INDEX: CN11.8, E626.1, RP501.7, U8.24
~INT2: CN15.1, P1.19, R191.2, U3.16, U7.21
~INT3: U2.17, U3.17
~INT6: P1.22, R192.2, U3.18, U8.21
~IORESET: E520.1, E615.1, U37.8
~IPL0: P1.40, RP102.7, U1.25, U3.13
~IPL1: P1.42, RP102.8, U1.24, U3.14
~IPL2: P1.44, RP102.9, U1.23, U3.15
~KBCLOCK: E632.3, RP501.2, U7.40
~KBDATA: E631.3, RP501.3, U7.39
~KBRESET: CN13.3, JP1.2, RP501.5, U5.5
~LDS: P1.70, RP101.5, U1.8, U2.51, U5.10
~LED: R503.2, R505.1, U7.3, U38.2
~LPEN: JP8.2, U2.78
~MTR0: CN11.4, CN11.16, R504.2, R506.1, U36.4
~MTRX: E613.1, U36.2
~MTR: U5.7, U8.17
~ODD_CIA: U7.23, U37.3
~OVR: CN15.2, P1.17, RP104.9, U5.29
~RAS0: U2.57, U35.2
~RAS1: U2.56, U35.4
~RDY: CN11.34, E611.1, U7.7
~RESET: U7.34, U8.34, U37.9, U37.11
~ROMEN: R114.1, U6.13
~RST: P1.53, RP101.4, U1.18, U2.16, U3.11, U5.41, U37.12
~RXD: U3.41, U39.3
~SEL0: CN11.10, J90.3, U5.16
~SEL1: CN11.12, E625.1, J90.4
~SEL2: E614.1, U8.15
~SEL3: E624.1, U8.16
~SIDE: CN11.32, E617.1, U8.12
~STEP: CN11.20, E622.1, U8.10
~TRK0: CN11.26, E619.1, U7.6
~TXD: U3.40, U38.9
~UDS: P1.72, RP101.6, U1.7, U2.52, U5.11
~VMA: P1.51, RP104.3, U1.19, U37.2, U37.5
~VPA: P1.48, R102.2, RP104.4, U1.21
~VSYNC: JP7B1.3, JP99V1.1, U2.79, U94.11
~WE: U2.21, U35.17
~WPROT: CN11.28, E618.1, U7.5
~XCLKEN: CN9.2, R403.2, U33.1

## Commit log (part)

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2025-11-25 Commit first A500Sub
2025-11-25 created gerbers
2026-01-06 updated rev 8A.2
2026-01-24 Added 3D models
2026-01-24 Built new Gerber files
2026-02-16 changed silkscreen thickness
